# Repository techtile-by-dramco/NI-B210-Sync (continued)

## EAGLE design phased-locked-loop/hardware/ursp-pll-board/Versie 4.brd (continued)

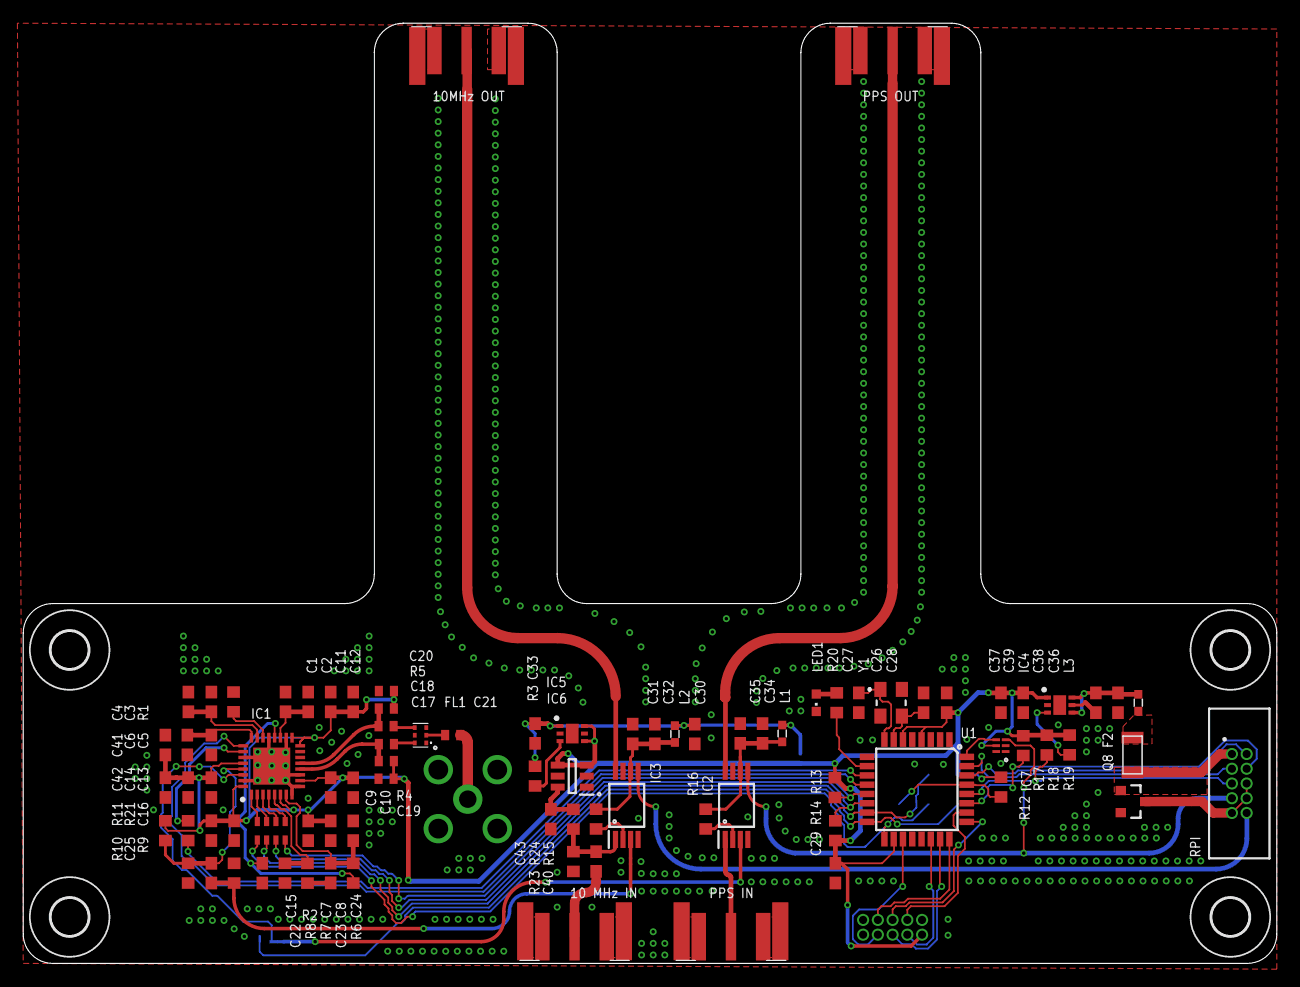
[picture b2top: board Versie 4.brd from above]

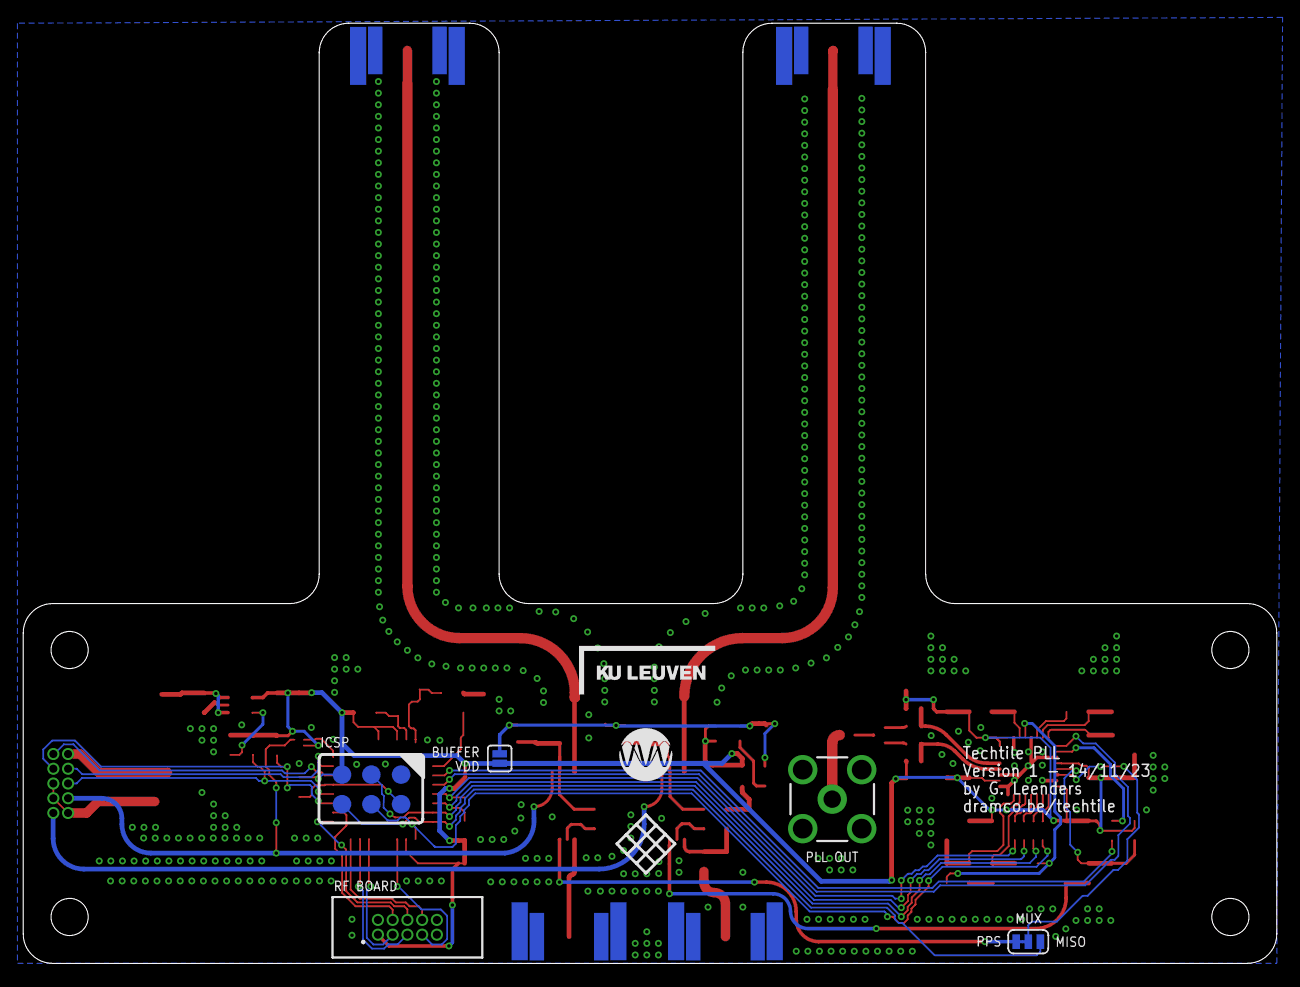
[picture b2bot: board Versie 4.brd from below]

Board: 2 copper layers, 108.0 x 81.0 mm, 101 parts (10 on the bottom side), 67 nets.

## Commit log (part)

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2023-01-20 test files rpi
2023-01-20 samples server
2023-01-20 changed samples dir
2023-01-20 added RX starts in... seconds
2023-01-20 rx time
2023-01-20 increased sample size
2023-01-20 samples ZC2
2023-01-20 samples ZC1
2023-01-20 samples ZC 2
2023-01-20 clean-up
2023-01-20 cleanup
2023-01-20 decreased sample size
2023-01-20 main to 10 sec record
2023-01-31 clean + 10MHz
2023-02-01 reduced file size
2023-02-01 abs time
2023-02-01 update rate
2023-02-01 tx from reading file
2023-02-01 added zc-sequence data
2023-02-03 update main to 1MHz
2023-06-02 update test 121
2023-06-12 update test 211
2023-09-27 Add octoclock validation folder
2023-09-27 update name folder
2023-09-27 Add pll folder
2023-09-27 Update octoclock arch. figure
2024-01-17 add folders to phased-locked-loop folder
2024-01-18 Added PLL things
2024-02-06 Rename Readme.md to README.md
2025-04-10 update files and results
2025-04-10 vcorate check
2025-04-11 update results
2025-10-02 update folder name 04_dual_rx_matrix_single_b210
2025-10-23 update 06
2025-10-23 Add results section to readme with plots
    Added results section with phase difference polar plots.
2025-10-23 Clean up commands in experiments/readme.md
    Removed redundant commands for processing and plotting in the readme.
2025-10-23 update figs
2025-10-23 Update readme with plot creation instructions
    Added instructions for creating plots using plot_mean_2d and plot_mean_std_angles scripts.
2025-10-23 add phase_difference plot 06
2025-10-23 update 07
2025-10-23 add 08
2025-10-27 add new exp 06 splitter type 2
2025-10-27 Fix image source link in README.md
2025-10-27 update 06 type 2 splitter
2025-10-27 add figs 06 type 2
2025-10-27 Update image links in README for phase difference results
2025-10-27 update max i and q
2025-10-27 plot max i and q
2025-10-27 update 06 type 2
2025-10-27 Update README with additional results plots
2025-10-30 Add README for multi USRP RX experiment
    Added detailed README for multi USRP RX experiment, including setup instructions, processing data, and results visualization.
2025-10-30 Revise README for multi USRP RX splitter experiment
    Updated README to clarify experiment details and corrections.
2025-10-30 Revise README for multi USRP RX experiment
    Updated README to clarify experimental setup and adjustments.
2025-10-30 create exp 20
2025-10-30 Results 20
2025-10-30 add exp 21
2025-10-30 results exp 21
2025-10-30 Create exp 21
2025-10-30 exp 22
2025-10-31 Update readme with multiple input directory commands
    Added additional commands for processing raw data from different directories.
2025-10-31 Update readme with plot creation instructions
    Added instructions for creating plots using plot_mean_std_angles.py.
2025-10-31 Document loopback experiments and settings
    Added details for loopback experiments including settings and results.
2025-10-31 Add Sync experiments section to readme
    Added section for Sync experiments and updated formatting.
2025-10-31 Fix command for storing individual phases
2025-10-31 add exp 30 & 31
2025-10-31 update 31
2025-10-31 update ip + server
2025-10-31 add tools.py
2025-11-05 exp update
2025-11-05 create exp 32
2025-11-06 add exp 33
2025-11-10 update 33
2025-11-14 update and reorganise
2025-11-14 Update image sizes in README results section
2025-11-14 Add results section to README for splitter comparison
    Added results section comparing outputs from same and different 2-way splitters with images.
2025-11-14 Fix image source URL in README.md
2025-11-18 Refactor conclusion section in README.md
    Removed redundant lines in the conclusion section of the README.
2025-11-18 add 32
2025-11-19 clean 32
2025-11-28 Update 32/33
